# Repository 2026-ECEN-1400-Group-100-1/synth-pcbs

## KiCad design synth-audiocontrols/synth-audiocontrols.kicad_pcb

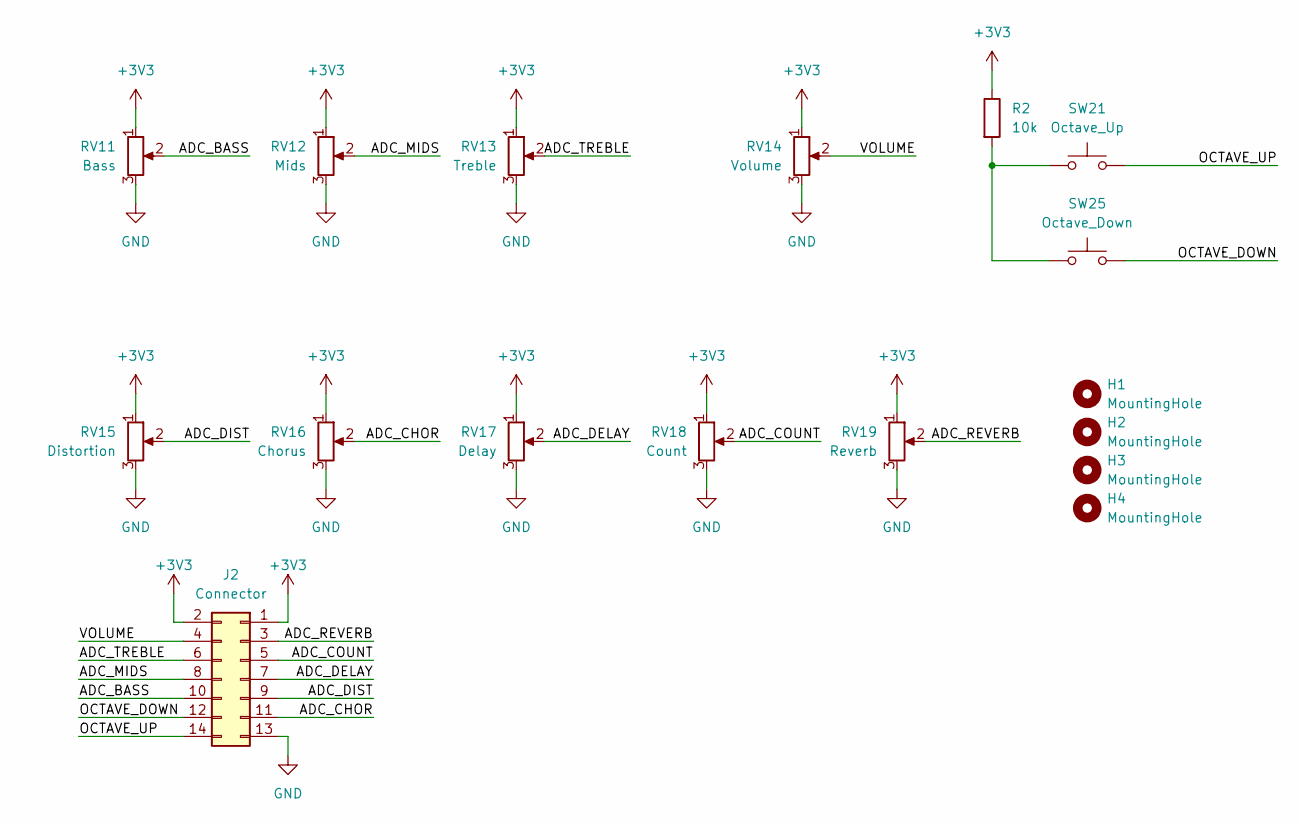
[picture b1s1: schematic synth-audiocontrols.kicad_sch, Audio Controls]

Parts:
H1, H2, H3, H4: MountingHole; MountingHole_3.2mm_M3
J2: Connector; IDC-Header_2x07_P2.54mm_Vertical
R2: 10k; R_0603_1608Metric_Pad0.98x0.95mm_HandSolder
RV11: Bass; Potentiometer_Bourns_3296W_Vertical
RV12: Mids; Potentiometer_Bourns_3296W_Vertical
RV13: Treble; Potentiometer_Bourns_3296W_Vertical
RV14: Volume; Potentiometer_Bourns_3296W_Vertical
RV15: Distortion; Potentiometer_Bourns_3296W_Vertical
RV16: Chorus; Potentiometer_Bourns_3296W_Vertical
RV17: Delay; Potentiometer_Bourns_3296W_Vertical
RV18: Count; Potentiometer_Bourns_3296W_Vertical
RV19: Reverb; Potentiometer_Bourns_3296W_Vertical
SW21: Octave_Up; SW_Cherry_MX_1.00u_PCB
SW25: Octave_Down; SW_Cherry_MX_1.00u_PCB

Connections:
+3V3: J2.1, J2.2, R2.1, RV11.1, RV12.1, RV13.1, RV14.1, RV15.1, RV16.1, RV17.1, RV18.1, RV19.1
/ADC_BASS: J2.10, RV11.2
/ADC_CHOR: J2.11, RV16.2
/ADC_COUNT: J2.5, RV18.2
/ADC_DELAY: J2.7, RV17.2
/ADC_DIST: J2.9, RV15.2
/ADC_MIDS: J2.8, RV12.2
/ADC_REVERB: J2.3, RV19.2
/ADC_TREBLE: J2.6, RV13.2
/OCTAVE_DOWN: J2.12, SW25.2
/OCTAVE_UP: J2.14, SW21.2
/VOLUME: J2.4, RV14.2
GND: J2.13, RV11.3, RV12.3, RV13.3, RV14.3, RV15.3, RV16.3, RV17.3, RV18.3, RV19.3
unnamed: R2.2, SW21.1, SW25.1

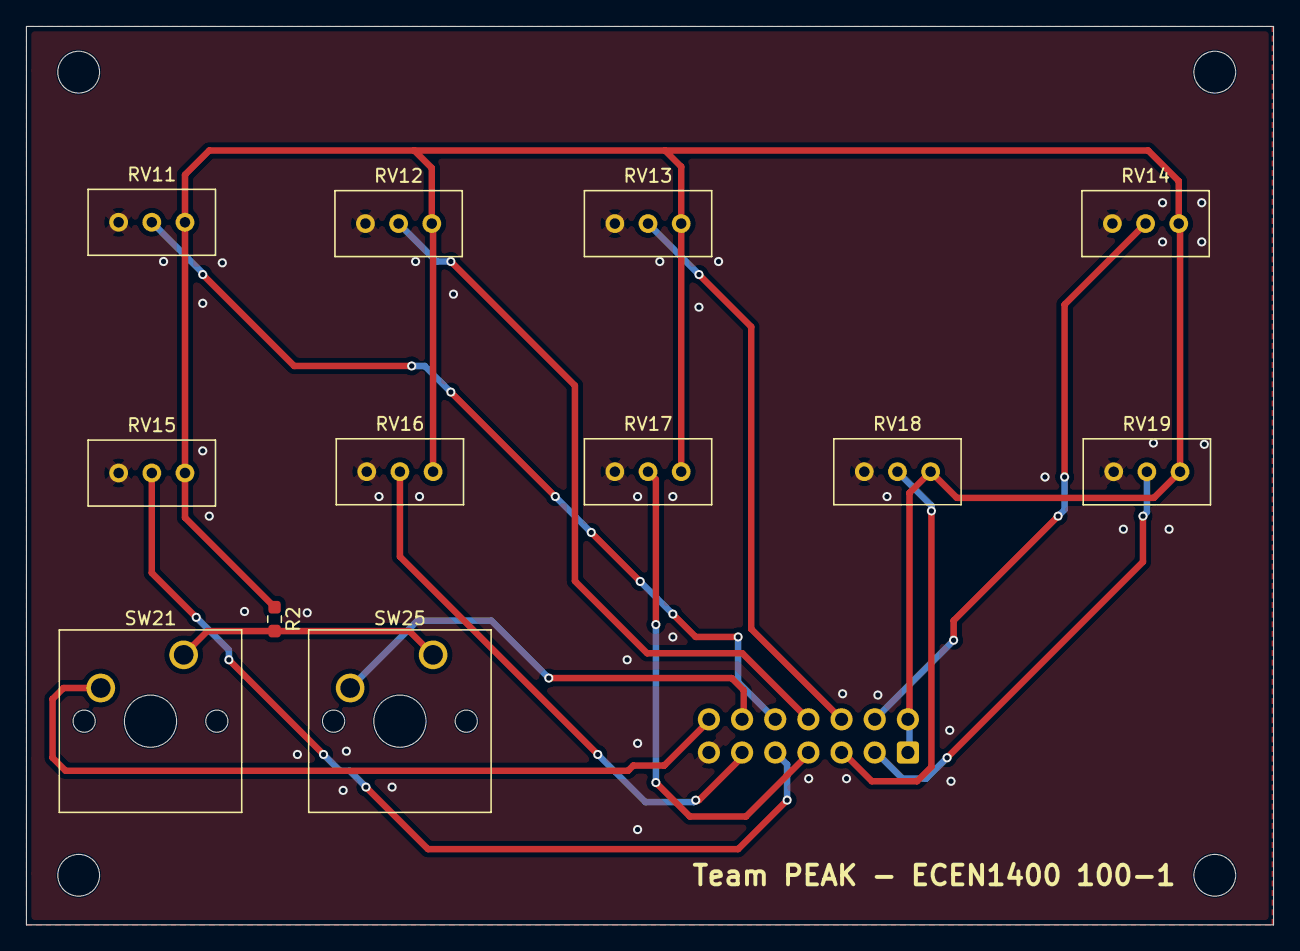
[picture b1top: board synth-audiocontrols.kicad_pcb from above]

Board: 2 copper layers, 95.5 x 68.8 mm, 17 parts (1 on the bottom side), 14 nets.

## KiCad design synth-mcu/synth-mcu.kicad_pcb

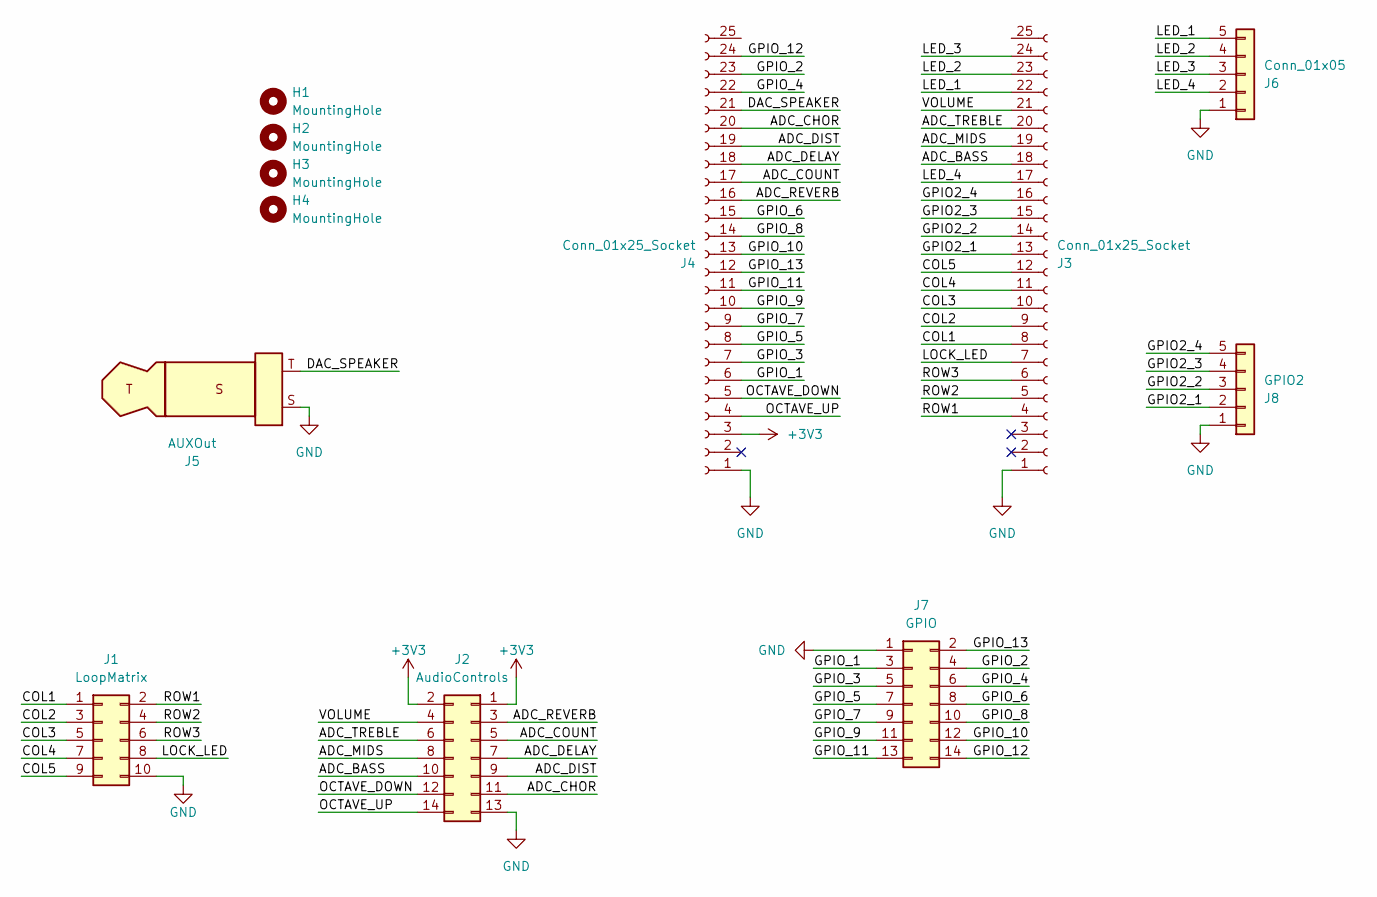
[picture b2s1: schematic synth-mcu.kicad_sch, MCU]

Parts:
H1, H2, H3, H4: MountingHole; MountingHole_3.2mm_M3
J1: LoopMatrix; IDC-Header_2x05_P2.54mm_Vertical
J2: AudioControls; IDC-Header_2x07_P2.54mm_Vertical
J3, J4: Conn_01x25_Socket; PinSocket_1x25_P2.54mm_Vertical
J5: AUXOut; AudioConnector_2092-STX-3000-ND
J6: Conn_01x05; Molex_KK-254_AE-6410-05A_1x05_P2.54mm_Vertical
J7: GPIO; IDC-Header_2x07_P2.54mm_Vertical
J8: GPIO2; Molex_KK-254_AE-6410-05A_1x05_P2.54mm_Vertical

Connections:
+3V3: J2.1, J2.2, J4.3
/ADC_BASS: J2.10, J3.18
/ADC_CHOR: J2.11, J4.20
/ADC_COUNT: J2.5, J4.17
/ADC_DELAY: J2.7, J4.18
/ADC_DIST: J2.9, J4.19
/ADC_MIDS: J2.8, J3.19
/ADC_REVERB: J2.3, J4.16
/ADC_TREBLE: J2.6, J3.20
/COL1: J1.1, J3.8
/COL2: J1.3, J3.9
/COL3: J1.5, J3.10
/COL4: J1.7, J3.11
/COL5: J1.9, J3.12
/DAC_SPEAKER: J4.21, J5.T
/GPIO2_1: J3.13, J8.2
/GPIO2_2: J3.14, J8.3
/GPIO2_3: J3.15, J8.4
/GPIO2_4: J3.16, J8.5
/GPIO_1: J4.6, J7.3
/GPIO_2: J4.23, J7.4
/GPIO_3: J4.7, J7.5
/GPIO_4: J4.22, J7.6
/GPIO_5: J4.8, J7.7
/GPIO_6: J4.15, J7.8
/GPIO_7: J4.9, J7.9
/GPIO_8: J4.14, J7.10
/GPIO_9: J4.10, J7.11
/GPIO_10: J4.13, J7.12
/GPIO_11: J4.11, J7.13
/GPIO_12: J4.24, J7.14
/GPIO_13: J4.12, J7.2
/LED_1: J3.22, J6.5
/LED_2: J3.23, J6.4
/LED_3: J3.24, J6.3
/LED_4: J3.17, J6.2
/LOCK_LED: J1.8, J3.7
/OCTAVE_DOWN: J2.12, J4.5
/OCTAVE_UP: J2.14, J4.4
/ROW1: J1.2, J3.4
/ROW2: J1.4, J3.5
/ROW3: J1.6, J3.6
/VOLUME: J2.4, J3.21
GND: J1.10, J2.13, J3.1, J4.1, J5.S, J6.1, J7.1, J8.1

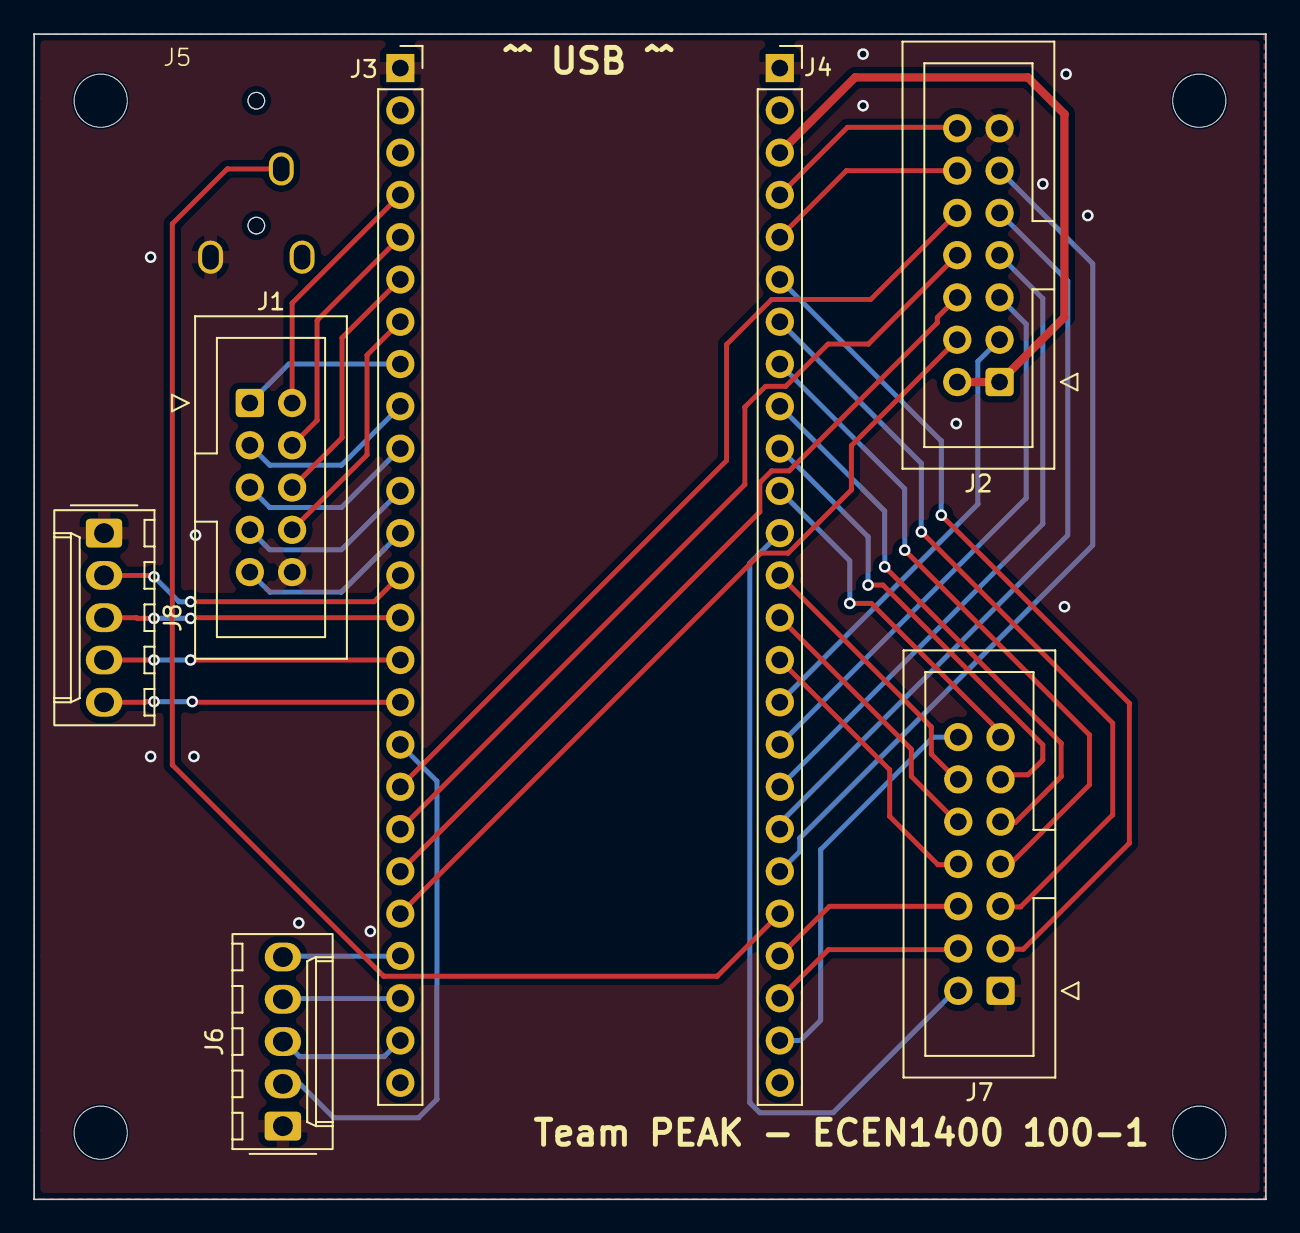
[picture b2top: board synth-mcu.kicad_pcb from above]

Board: 2 copper layers, 74.0 x 70.0 mm, 12 parts (0 on the bottom side), 44 nets.

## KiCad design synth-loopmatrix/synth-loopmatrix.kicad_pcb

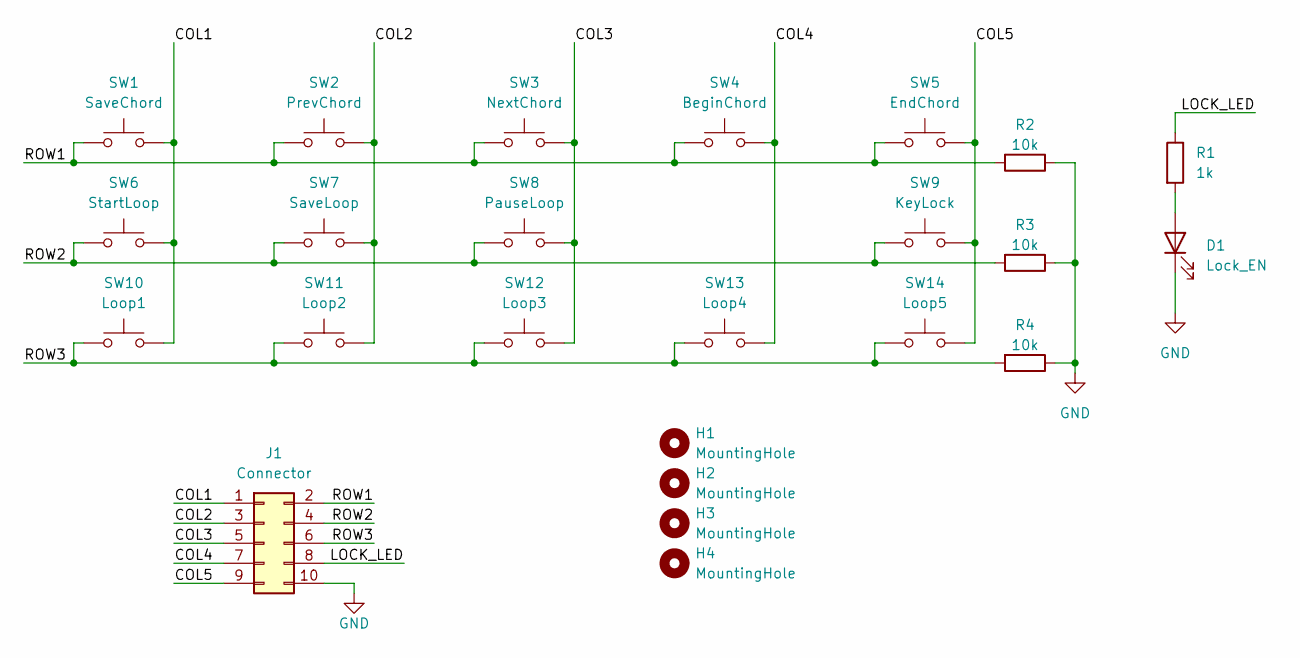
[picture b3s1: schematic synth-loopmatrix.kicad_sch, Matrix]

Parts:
D1: Lock_EN; LED_0603_1608Metric_Pad1.05x0.95mm_HandSolder
H1, H2, H3, H4: MountingHole; MountingHole_3.2mm_M3
J1: Connector; IDC-Header_2x05_P2.54mm_Vertical
R1: 1k; R_0603_1608Metric_Pad0.98x0.95mm_HandSolder
R2, R3, R4: 10k; R_0603_1608Metric_Pad0.98x0.95mm_HandSolder
SW1: SaveChord; SW_Cherry_MX_1.00u_PCB
SW2: PrevChord; SW_Cherry_MX_1.00u_PCB
SW3: NextChord; SW_Cherry_MX_1.00u_PCB
SW4: BeginChord; SW_Cherry_MX_1.00u_PCB
SW5: EndChord; SW_Cherry_MX_1.00u_PCB
SW6: StartLoop; SW_Cherry_MX_1.00u_PCB
SW7: SaveLoop; SW_Cherry_MX_1.00u_PCB
SW8: PauseLoop; SW_Cherry_MX_1.00u_PCB
SW9: KeyLock; SW_Cherry_MX_1.00u_PCB
SW10: Loop1; SW_Cherry_MX_1.00u_PCB
SW11: Loop2; SW_Cherry_MX_1.00u_PCB
SW12: Loop3; SW_Cherry_MX_1.00u_PCB
SW13: Loop4; SW_Cherry_MX_1.00u_PCB
SW14: Loop5; SW_Cherry_MX_1.00u_PCB

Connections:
/COL1: J1.1, SW1.2, SW6.2, SW10.2
/COL2: J1.3, SW2.2, SW7.2, SW11.2
/COL3: J1.5, SW3.2, SW8.2, SW12.2
/COL4: J1.7, SW4.2, SW13.2
/COL5: J1.9, SW5.2, SW9.2, SW14.2
/LOCK_LED: J1.8, R1.1
/ROW1: J1.2, R2.2, SW1.1, SW2.1, SW3.1, SW4.1, SW5.1
/ROW2: J1.4, R3.2, SW6.1, SW7.1, SW8.1, SW9.1
/ROW3: J1.6, R4.2, SW10.1, SW11.1, SW12.1, SW13.1, SW14.1
GND: D1.1 (K), J1.10, R2.1, R3.1, R4.1
unnamed: D1.2 (A), R1.2

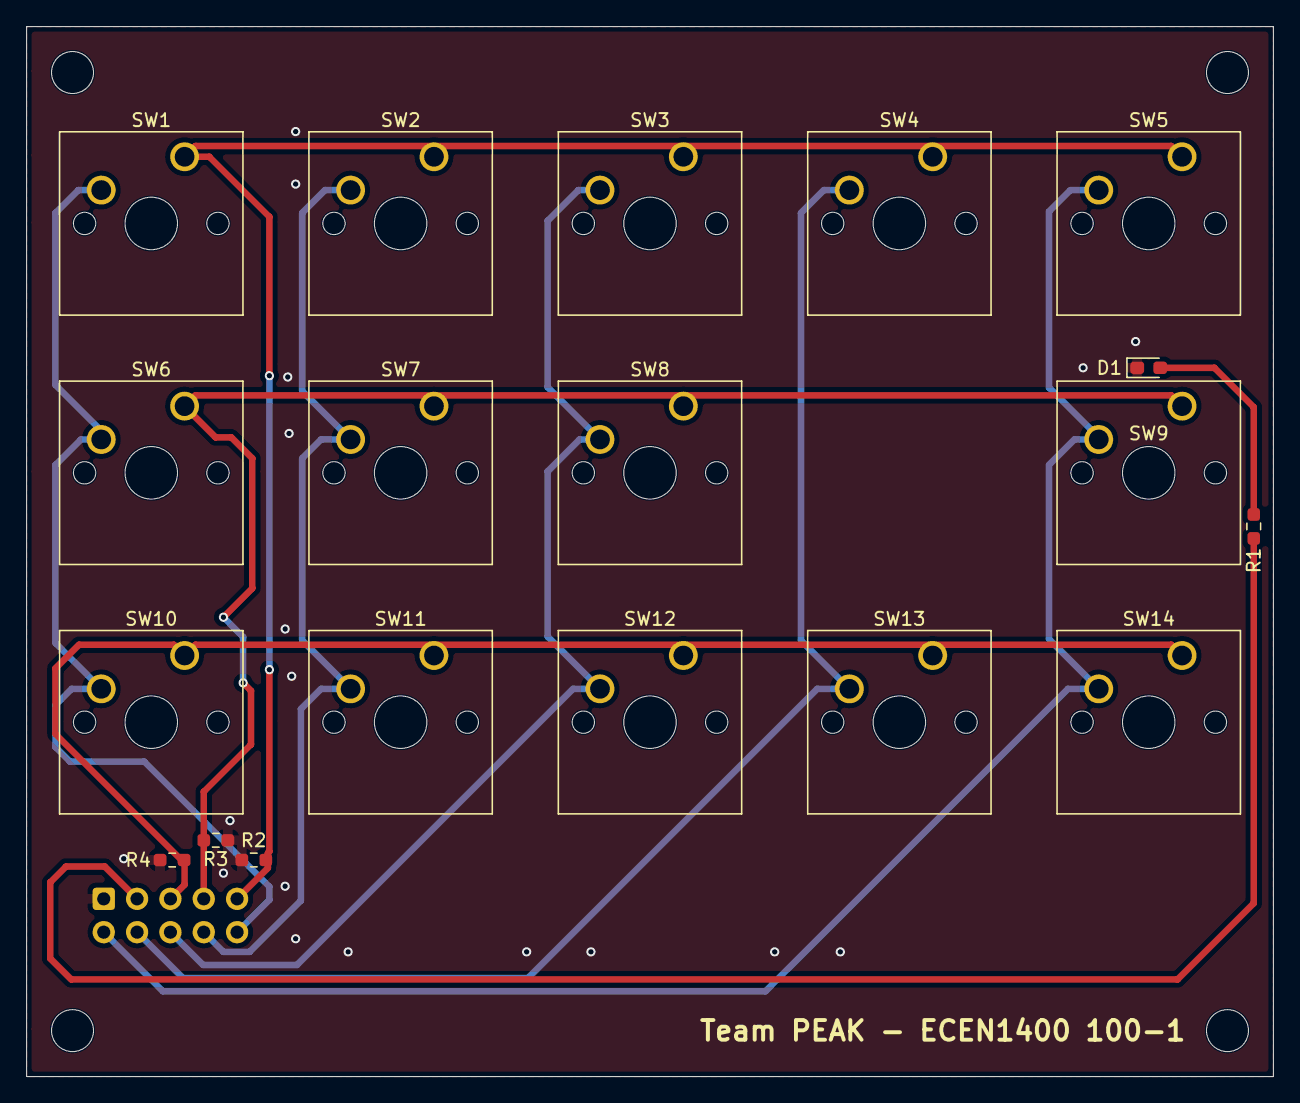
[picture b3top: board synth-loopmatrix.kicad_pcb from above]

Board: 2 copper layers, 95.0 x 80.0 mm, 24 parts (1 on the bottom side), 11 nets.
